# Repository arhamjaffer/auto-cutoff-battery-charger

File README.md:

# auto-cutoff-battery-charger
 PCB-based charging circuit with automatic cut-off; optimized for safe long-term operation
<div align="center">

</div>

---

## 📌 Overview

An **automatic battery charger with cut-off protection** — designed to safely charge a **12V lead-acid battery** and automatically disconnect when fully charged, preventing overcharging and extending battery life.

This project covers the **full PCB design cycle**: circuit design, schematic capture in KiCad, component selection, PCB layout, and fabrication-ready Gerber export.

> Designed as part of my circuit design & PCB prototyping work at NUST-PNEC.

---

## 🖼️ Board Preview

> *(Add your PCB layout screenshot or 3D render here)*

| Schematic | PCB Layout | 3D View |
|-----------|------------|---------|
|  |  |  |

---

## ⚙️ Specifications

| Parameter | Value |
|-----------|-------|
| **Input Voltage** | 14–15V DC (from transformer + rectifier) |
| **Output / Charging Voltage** | 13.8V – 14.4V (12V battery) |
| **Cut-Off Voltage** | ~14.4V (fully charged threshold) |
| **Max Charging Current** | ~1A |
| **Battery Type** | 12V Lead-Acid / SLA |
| **Cut-Off Mechanism** | Comparator-based (LM358 / LM393) |
| **Indication** | LED — Charging (Red) / Full (Green) |
| **Protection** | Overcharge cut-off, Reverse polarity |
| **PCB Layers** | 2-Layer |
| **EDA Tool** | KiCad |

---

## 🔋 How It Works

```
AC Mains Input
      ↓
Transformer (Step-Down)
      ↓
Bridge Rectifier (1N4007 × 4)
      ↓
Filter Capacitor (Smoothing)
      ↓
Voltage Regulator / Charging Stage
      ↓
Comparator Circuit (LM358)
   monitors battery voltage continuously
      ↓
   Battery Voltage < 14.4V  →  Relay ON  →  Charging continues  🔴 LED
   Battery Voltage ≥ 14.4V  →  Relay OFF →  Charging stops      🟢 LED
      ↓
Battery (12V Lead-Acid)
```

The heart of this circuit is the **LM358 op-amp comparator** — it compares the battery terminal voltage against a fixed reference (set via a voltage divider using a potentiometer). When battery voltage crosses the threshold, the comparator output switches, triggering the **relay to cut off charging automatically**.

---

## 🗂️ Project Structure

```
auto-cutoff-battery-charger/
│
├── 📁 Schematic/
│   └── battery_charger.kicad_sch      # Full schematic
│
├── 📁 PCB/
│   └── battery_charger.kicad_pcb      # PCB layout
│
├── 📁 Gerbers/
│   ├── battery_charger-F_Cu.gbr       # Front copper
│   ├── battery_charger-B_Cu.gbr       # Back copper
│   ├── battery_charger-F_Silkscreen.gbr
│   ├── battery_charger-B_Silkscreen.gbr
│   ├── battery_charger-F_Mask.gbr
│   ├── battery_charger-B_Mask.gbr
│   ├── battery_charger-Edge_Cuts.gbr  # Board outline
│   └── battery_charger.drl            # Drill file
│
├── 📁 BOM/
│   └── BOM.csv                        # Bill of Materials
│
├── 📁 images/
│   ├── schematic.png
│   ├── pcb_layout.png
│   └── 3d_render.png
│
└── README.md
```

---

## 🔩 Bill of Materials

| # | Component | Value / Part | Package | Qty |
|---|-----------|-------------|---------|-----|
| 1 | Op-Amp Comparator | LM358 / LM393 | DIP-8 / SOP-8 | 1 |
| 2 | Relay | 12V SPDT | PCB Mount | 1 |
| 3 | Relay Driver Transistor | BC547 / 2N2222 | TO-92 | 1 |
| 4 | Rectifier Diodes | 1N4007 | DO-41 | 4 |
| 5 | Flyback Diode | 1N4007 | DO-41 | 1 |
| 6 | Voltage Regulator | LM7812 / LM317 | TO-220 | 1 |
| 7 | Trimmer Potentiometer | 10kΩ | 3296W | 1 |
| 8 | Resistors | 1kΩ, 4.7kΩ, 10kΩ | 0805 / TH | 6 |
| 9 | Filter Capacitor | 1000µF / 25V | Electrolytic | 1 |
| 10 | Decoupling Capacitor | 100nF | 0805 | 2 |
| 11 | LED (Charging) | Red | 3mm / 0805 | 1 |
| 12 | LED (Full) | Green | 3mm / 0805 | 1 |
| 13 | LED Resistors | 470Ω | 0805 | 2 |
| 14 | Screw Terminals | 2-pin | 5.08mm | 3 |
| 15 | Fuse Holder + Fuse | 1A | PCB Mount | 1 |

> Full BOM available in [`/BOM/BOM.csv`](BOM/BOM.csv)

---

## 🛠️ Design Workflow

```
1. Circuit Design & Hand Calculations
        ↓
2. Schematic Capture (KiCad Schematic Editor)
        ↓
3. Component Selection & Footprint Assignment
        ↓
4. Netlist Export → PCB Editor
        ↓
5. PCB Layout & Component Placement
        ↓
6. Trace Routing (Power traces wider — 1.5mm+)
        ↓
7. Design Rule Check (DRC) — 0 errors
        ↓
8. Gerber Export (Fabrication-ready)
```

---

## ⚠️ Safety Features

| Feature | Implementation |
|---------|---------------|
| **Overcharge Protection** | Relay cuts off at ~14.4V via comparator |
| **Reverse Polarity Protection** | Diode at battery input |
| **Overcurrent Protection** | Inline fuse (1A) |
| **Flyback Protection** | Freewheeling diode across relay coil |
| **Visual Indication** | Red = Charging, Green = Full |

---

## 🏭 How to Fabricate

1. Download the [`/Gerbers/`](Gerbers/) folder
2. Zip all `.gbr` and `.drl` files
3. Upload to your preferred PCB fab:
   - [JLCPCB](https://jlcpcb.com) ← recommended, cheapest
   - [PCBWay](https://www.pcbway.com)
   - [OSH Park](https://oshpark.com)
4. Recommended settings: **2 layers, 1.6mm thickness, HASL finish**

---

## 🔓 How to Open in KiCad

```bash
# Clone the repository
git clone https://github.com/arhamjaffer/auto-cutoff-battery-charger.git

# Open in KiCad
# File → Open Project → select battery_charger.kicad_pro
```

> ⚠️ Requires **KiCad 6.0 or later**. KiCad 10.0 recommended.

---

## 📸 Design Highlights

- ✅ Comparator-based automatic cut-off — no microcontroller needed
- ✅ Adjustable cut-off voltage via onboard trimmer pot
- ✅ Clear dual-LED charging status indication
- ✅ Power traces sized for current capacity (1A+)
- ✅ Proper relay flyback protection
- ✅ Screw terminals for easy battery & input connection
- ✅ Fabrication-ready Gerbers included

---

## 🧪 Testing & Calibration

Once assembled:

1. **Set cut-off voltage** — connect a bench power supply set to **14.4V**, adjust the trimmer pot until the relay clicks OFF and green LED lights
2. **Test charging** — connect a discharged 12V battery; red LED should glow and current should flow
3. **Verify cut-off** — as battery reaches full charge (~14.4V), relay should disconnect automatically
4. **Check fuse** — replace with correct 1A rating before use with mains-derived supply

> ⚡ **Warning:** If using with a mains transformer, ensure proper isolation and follow electrical safety practices. High voltage is dangerous.

---

## 🙋 Author

**Arham Jaffer**
B.E. Electrical Engineering — NUST-PNEC, Karachi 🇵🇰
Co-Founder @ [GenXi Tech Solutions](https://www.genxitechsolutions.com/)

---

## 📄 License

This project is open-source under the [MIT License](LICENSE). Feel free to use, modify, and build upon it — just give credit!

---

<div align="center">

</div>

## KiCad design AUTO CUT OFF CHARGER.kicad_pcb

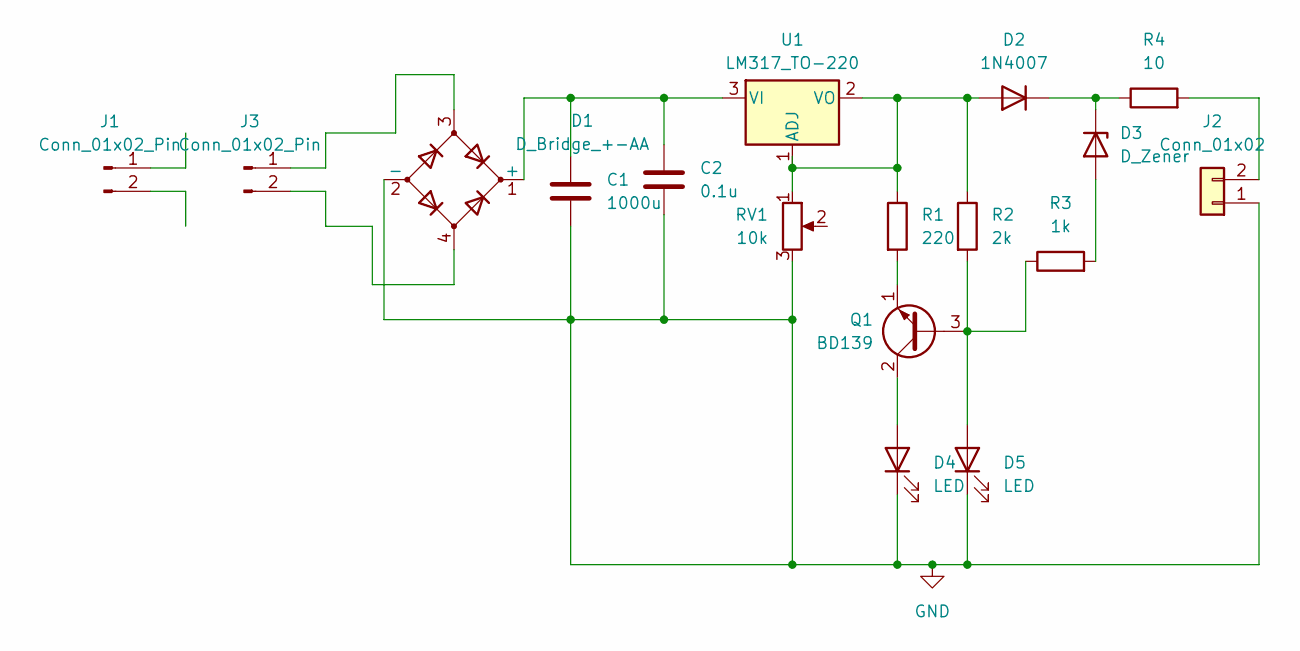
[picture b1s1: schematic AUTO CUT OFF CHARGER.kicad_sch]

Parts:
C1: 1000u; CP_Radial_D10.0mm_P5.00mm
C2: 0.1u; CP_Radial_D10.0mm_P5.00mm
D1: D_Bridge_+-AA; Diode_Bridge_Round_D9.8mm
D2: 1N4007; D_DO-41_SOD81_P10.16mm_Horizontal
D3: D_Zener; D_DO-41_SOD81_P10.16mm_Horizontal
D4, D5: LED; LED_D5.0mm
J1, J3: Conn_01x02_Pin; PinHeader_1x02_P2.54mm_Vertical
J2: Conn_01x02; PinHeader_1x02_P2.54mm_Vertical
Q1: BD139; TO-126-3_Vertical
R1: 220; R_Axial_DIN0207_L6.3mm_D2.5mm_P10.16mm_Horizontal
R2: 2k; R_Axial_DIN0207_L6.3mm_D2.5mm_P10.16mm_Horizontal
R3: 1k; R_Axial_DIN0207_L6.3mm_D2.5mm_P10.16mm_Horizontal
R4: 10; R_Axial_DIN0207_L6.3mm_D2.5mm_P10.16mm_Horizontal
RV1: 10k; Potentiometer_Bourns_3296W_Vertical
U1: LM317_TO-220; TO-220-3_Vertical

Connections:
GND: C1.2, C2.2, D1.2 (-), D4.1 (K), D5.1 (K), J2.1, RV1.3
unnamed: C1.1, C2.1, D1.1 (+), U1.3 (VI)
unnamed: D2.2 (A), R1.1, R2.1, RV1.1, U1.1 (ADJ), U1.2 (VO)
unnamed: D2.1 (K), D3.1 (K), R4.1
unnamed: D3.2 (A), R3.2
unnamed: D4.2 (A), Q1.2 (C)
unnamed: D5.2 (A), Q1.3 (B), R2.2, R3.1
unnamed: J2.2, R4.2
unnamed: D1.3, J3.1
unnamed: D1.4, J3.2
unnamed: Q1.1 (E), R1.2

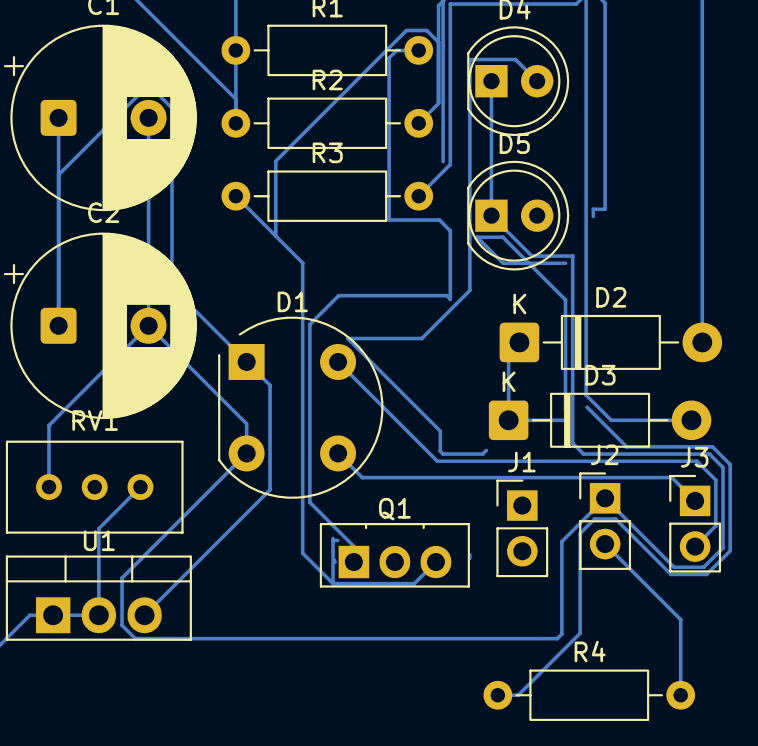
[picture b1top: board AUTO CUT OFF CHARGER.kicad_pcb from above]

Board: 2 copper layers, 17 parts (0 on the bottom side), 11 nets.

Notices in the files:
README.md:
License: MIT
